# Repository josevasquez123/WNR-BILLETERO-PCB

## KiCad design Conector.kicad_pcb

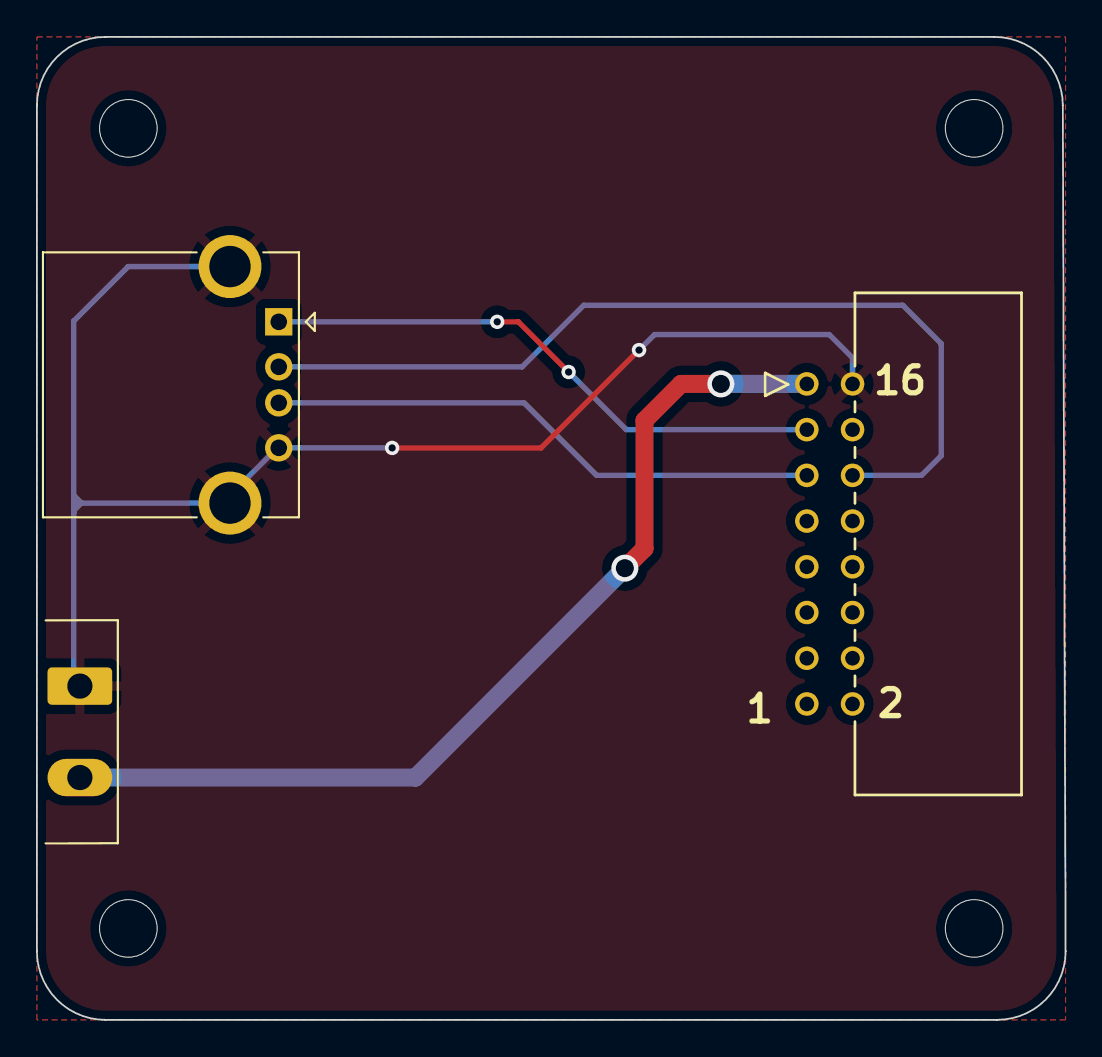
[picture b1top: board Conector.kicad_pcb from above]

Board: 2 copper layers, 57.1 x 54.6 mm, 7 parts (0 on the bottom side), 5 nets.

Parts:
H100, H101, H102, H103: MountingHole; MountingHole_3.2mm_M3
J100: VCC_BORNERA; PhoenixContact_MSTBA_2,5_2-G-5,08_1x02_P5.08mm_Horizontal
J101: USB; USB_A_CONNFLY_DS1095-WNR0
J103: XG4C-1634; CONN_XG4C-1634_OMR

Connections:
+5V: J101.1 (VBUS), J103.3
+12V: J100.2, J103.1
/D+: J101.3 (D+), J103.5
/D-: J101.2 (D-), J103.6
GND: J100.1, J101.4 (GND), J101.5 (Shield), J103.2

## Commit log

2023-10-11 acabado V1
